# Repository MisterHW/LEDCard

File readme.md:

# LEDCard

A credit card - sized, slim Li-Ion battery powered LED ring light for better macro shots everywhere you go.

## Revisions

Only revision 1E files (Eagle 7 format) were recovered at the time of this writing. Nevertheless, images and information about earlier versions are provided below to illustrate thoughts and decisions.

### LEDCard-1A : first prototype

Ideas:

- LED ring light
- macro lens
- battery-powered
- notches to be able to fix it to a device with rubber bands

Classic mistake: the photomask was flipped, so the SOT23-5 IC also had to be assembled on its back. Macro shot for entertainment purposes:

Insights:

- LED efficiency too low (~50 lm/W)
- CR2032 batteries inadequate
- Inrush current may lead to contact degradation of the push button over time.
- Rubber band idea turned out to be more of a fight than a feature. Covering the bottom side with tape may be more effective to prevent the board from sliding around on the smartphone. When combined with elastomeric protective cases, no additional material may be needed.

Switch from FAN5331 (Rds(ON) = 0.5 Ohm, 1.6 MHz) to LM3410Y (Rds(ON) = 0.17 Ohm, 0.525 MHz and 1.6 MHz options):

<table><thead><tr>
<td><a href="doc/FAN5331.pdf">FAN5331</a></td>
<td><a href="doc/LM3410.pdf">LM3410</a></td>
</tr></thead><tbody><tr>
<td></td>
<td></td>
</tr></tbody></table>

### LEDCard-1D : LIR2430 cells and charging via USB

Ideas:
- Switch to LIR2430 rechargable Li-Ion button cells (60-70 mAh, Ichg = 50 mA, RS Part No.: 183-4294)
- Push button now switches ENA instead of VCC.
- Two power levels (ON / ON+HI) for medium and max brightness.
- Replace FAN5331 with LM3410.

Insights:

- Li-Ion cells can deep discharge and be destroyed.
- MCP73831 Li-Ion charging IC developed an intermittent solder joint failure after > 1 year of use in wallet, probably due to flexural stresses. Switch to MSOP recommended. Resolved by reflowing with pre-heater and hot air.
- 1.0mm FR4 is not stiff enough. Switch to 0.4mm or 0.6 mm FR4 and laminate onto laser-cut and deburred Ti sheet metal (see cad/ folder for .dxf file).
- ON button should raise MCP73831 charge current to allow USB-powered operation with a cable plugged in.

### LEDCard-1E : Battery Protection Update, Half-Press Button, Low Batt TEST

Ideas:

- Disable the boost converter when battery voltage under load drops below 2.5V (internal resistance is significant, maximum discharge current 2*60 mA is not great but can only be addressed with better / bigger cells or fragile pouch cells).
- Manage two power levels with a single push button that allows intuitive half / full press.
- Battery Level Test: half-press SW1 so the LED light turns on. When pressing TEST, the LEDs should turn off. Once they stay lit, the battery level is low. This works by forming a voltage divider to VCC. As VCC drops, FB is low enough to cause the boost converter to turn back on.
- TEST button at the edge does not cause the LEDCard to turn on when pressed accidentally.

Insights:

- Half press button is unpleasant, needs a printed / formed button cap to be useful. Idea to shield the button with battery clips around it is effective at preventing accidental presses, but also makes use harder.
- Tantalum capacitor in the picture was experimental and helped demonstrate that operation with USB connected is not possible without raising the charger current in LED on mode.
- SMD slider switch would be nice to enable continuous / hands-free operation (especially when USB is plugged in).
- USB-C to be considered for next iteration.
- LIR2430 cell found to be dead after 2 years of storage. Remove cells when not in use for > 4 weeks.
- FR4 front cover / diffusor would be nice. maybe 3D print with clear PETG?

#### LEDCard-1E Schematic

#### LEDCard-1E Layout

#### Lenses

16.5mm diameter plano-convex molded acrylic lenses:

- f = +49 mm, https://astromedia.de/Opti-Media-Linse-OM4
- f = +65 mm, https://astromedia.de/Opti-Media-Linse-OM5
- f = +120 mm, https://astromedia.de/Opti-Media-Linse-OM6

Mounted with clear epoxy (Uhu Endfest). For mounting, put Al tape on the back of the LEDCard PCB and place the lens in its designated location. Rub the tape to get complete adhesion without air pockets to avoid seeping of the epoxy.

### Known Issues

Please see https://github.com/MisterHW/LEDCard/issues?q= where known problems are listed and improvements are discussed.

## License

Copyright Helge Wurst 2022.

This source describes Open Hardware and is licensed under the CERN-OHL-S v2.

You may redistribute and modify this source and make products using it under the terms of the CERN-OHL-S v2 (https://ohwr.org/cern_ohl_s_v2.txt).

This source is distributed WITHOUT ANY EXPRESS OR IMPLIED WARRANTY, INCLUDING OF MERCHANTABILITY, SATISFACTORY QUALITY AND FITNESS FOR A PARTICULAR PURPOSE. Please see the CERN-OHL-S v2 for applicable conditions.

Source location: https://github.com/MisterHW/LEDCard

As per CERN-OHL-S v2 section 4, should You produce hardware based on this source, You must where practicable maintain the Source Location visible on the external case of the Gizmo or other products you make using this source.

## Changes

* 2023-01: License information added.
* 2022-12: Project files recovered, documentation added. First release.
* 2017: Project started.

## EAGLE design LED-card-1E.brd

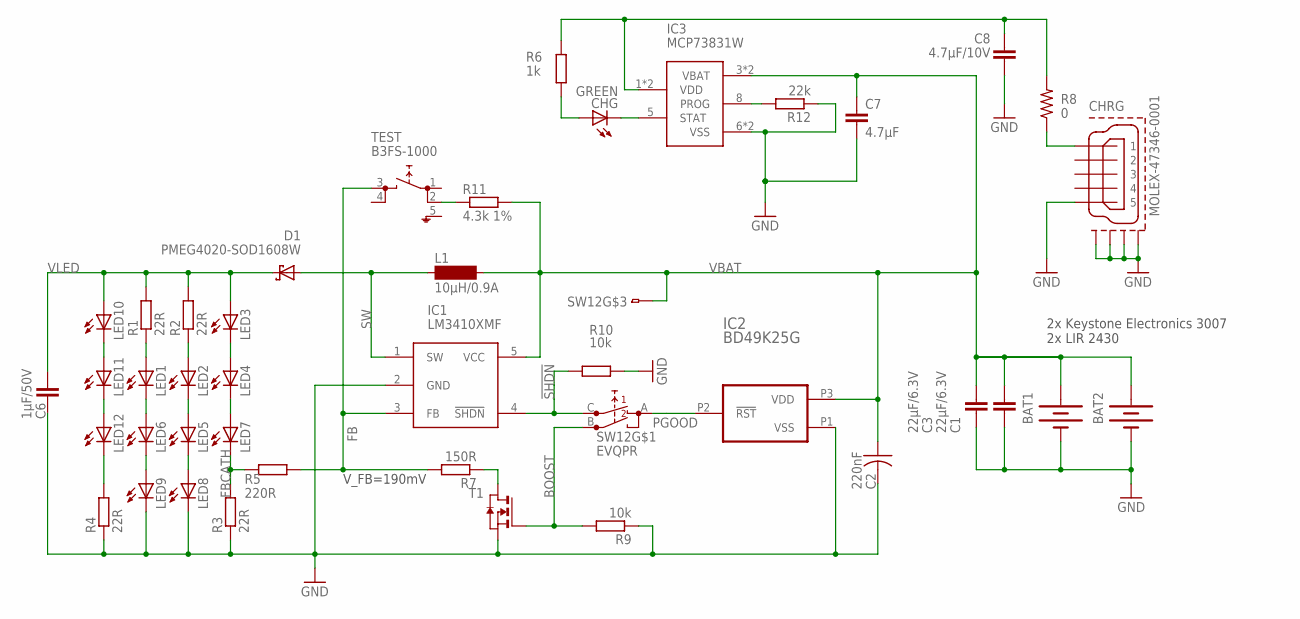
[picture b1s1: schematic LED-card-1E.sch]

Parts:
BAT1, BAT2: BATTERY; BATTCON_245MM; MPN 3007; MOUSER 534-3007
C1, C3: 22µF/6.3V; C0805K
C2: 220nF; C0805K
C6: 1µF/50V; C0805K
C7: 4.7µF; C0603K
C8: 4.7µF/10V; C0603K
CHG: GREEN; CHIPLED-0603-TTW
CHRG: MOLEX-47346-0001; MOLEX-47364-0001
D1: PMEG4020-SOD1608W; SOD1608W; MOUSER 771-PMEG4020EPK,315
IC1: LM3410XMF; SOT23-5L; MPN LM3410XMF; MOUSER 926-LM3410XMF/NOPB
IC2: BD49K25G; SOT-23
IC3: MCP73831W; DFN8W
L1: 10µH/0.9A; MS50; MPN CBC3225T100KR; MOUSER CBC3225T100KR
LED1, LED2, LED3, LED4, LED5, LED6, LED7, LED8, LED9, LED10, LED11, LED12: LEDSML1206; SML1206; MPN 158301260; MOUSER 710-158301260
R1, R2, R3, R4: 22R; R0805
R5: 220R; R0603
R6: 1k; R0603
R7: 150R; R0603
R8: 0; 0805
R9, R10: 10k; R0603
R11: 4.3k 1%; R0603
R12: 22k; R0603
SW12: EVQPR; EVQPR-GND; MF_PARTNO EVQ-PRHA09; MOUSER 667-EVQ-PRHA09
T1: NMOSSOT23; SOT-23
TEST: B3FS-1000; SKHMPXE010; MPN B3FS-1000; MOUSER 653-B3FS-1000

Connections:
!SHDN: IC1.4 (!SHDN), R10.1, SW12.C (1.1)
BOOST: R9.2, SW12.B (1.2), T1.3 (G)
FB: IC1.3 (FB), R5.1, R7.2, TEST.3 (2.1)
FBCATH: LED7.C, R3.2, R5.2
FBLO: R7.1, T1.1 (D)
GND: BAT1.2 (-), BAT2.2 (-), C1.2, C2.2, C3.2, C6.2, C7.2, C8.2, CHRG.5, CHRG.GND1, CHRG.GND2, CHRG.GND3, CHRG.GND4, IC1.2 (GND), IC2.P1 (VSS), IC3.6 (VSS), IC3.GND (VSS), LED8.C, LED9.C, R3.1, R4.1, R9.1, R10.2, R12.1, T1.2 (S)
unnamed: R11.1, TEST.2 (1.2)
unnamed: IC3.8 (PROG), R12.2
unnamed: LED1.A, R1.1
unnamed: LED3.C, LED4.A
unnamed: LED2.C, LED5.A
unnamed: LED1.C, LED6.A
unnamed: LED6.C, LED9.A
unnamed: LED5.C, LED8.A
unnamed: LED4.C, LED7.A
unnamed: CHG.C@1 (C), IC3.5 (STAT)
unnamed: LED2.A, R2.1
unnamed: CHG.A@1 (A), R6.1
unnamed: CHRG.1, R8.1
unnamed: LED10.C, LED11.A
unnamed: LED11.C, LED12.A
unnamed: LED12.C, R4.2
PGOOD: IC2.P2 (!RST), SW12.A (2.1)
SW: D1.A, D1.A2 (A), IC1.1 (SW), L1.1
VBAT: BAT1.1 (+), BAT1.3 (+), BAT2.1 (+), BAT2.3 (+), C1.1, C2.1, C3.1, C7.1, IC1.5 (VCC), IC2.P3 (VDD), IC3.3 (VBAT), IC3.4 (VBAT), L1.2, R11.2, SW12.D (1)
VBUS: C8.1, IC3.1 (VDD), IC3.2 (VDD), R6.2, R8.2
VLED: C6.1, D1.C, D1.C2 (C), LED3.A, LED10.A, R1.2, R2.2

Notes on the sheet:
2x Keystone Electronics 3007 2x LIR 2430
V_FB=190mV

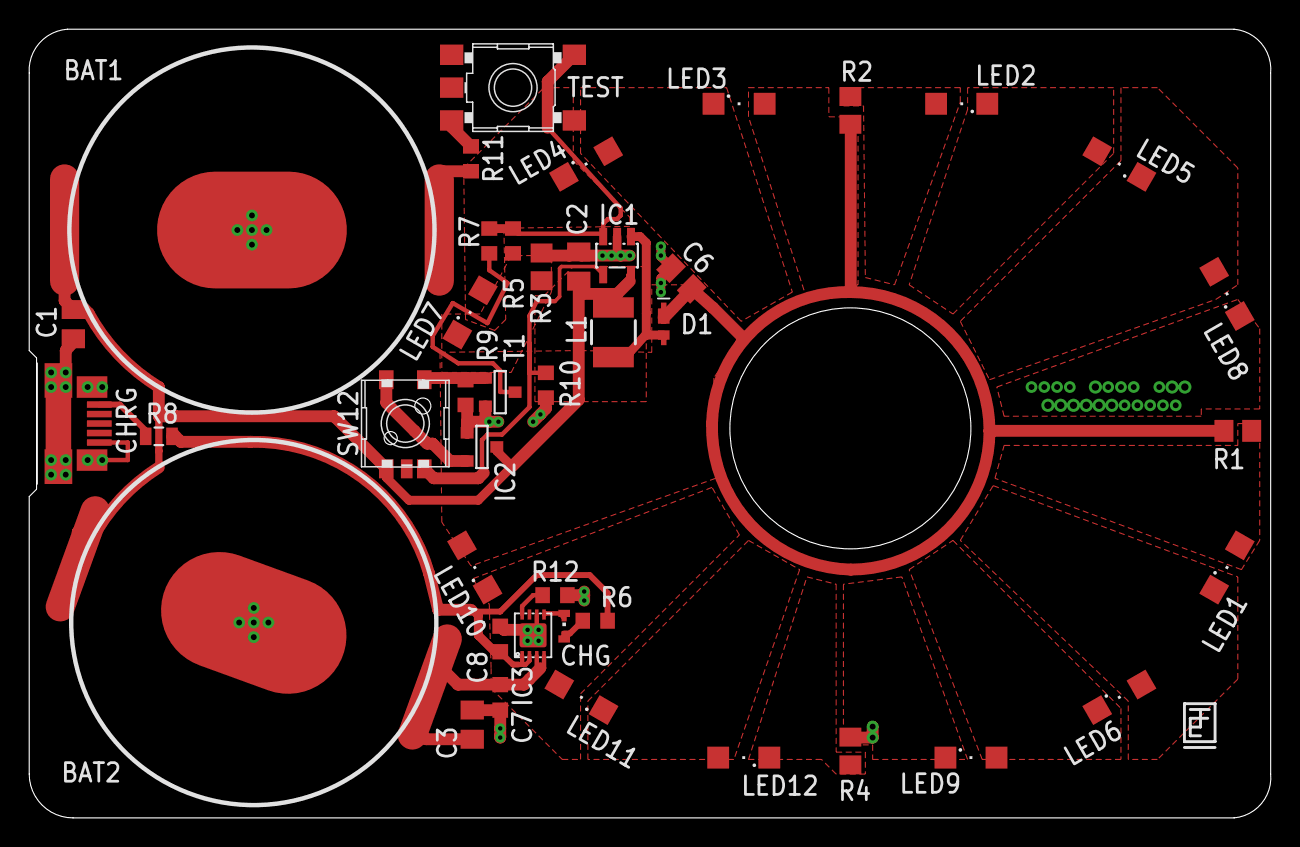
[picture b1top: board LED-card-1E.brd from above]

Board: 2 copper layers, 85.0 x 54.0 mm, 43 parts (0 on the bottom side), 27 nets.

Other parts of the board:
U$1: DESIGNER

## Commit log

2022-12-30 initial release
2022-12-31 add comments
2022-12-31 append info
2022-12-31 comments added
2022-12-31 append lens info
2023-01-02 add license info
2023-01-02 Add remark on known issues
    After a potential issue became known (stuck `TEST` active during transport and storage can deep discharge and damage Li-Ion cells), it is recommended to check open issues.

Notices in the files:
parts and their libraries:
SparkFun-Passives: Licensing: CC v3.0 Share-Alike You are welcome to use this library for commercial purposes.
